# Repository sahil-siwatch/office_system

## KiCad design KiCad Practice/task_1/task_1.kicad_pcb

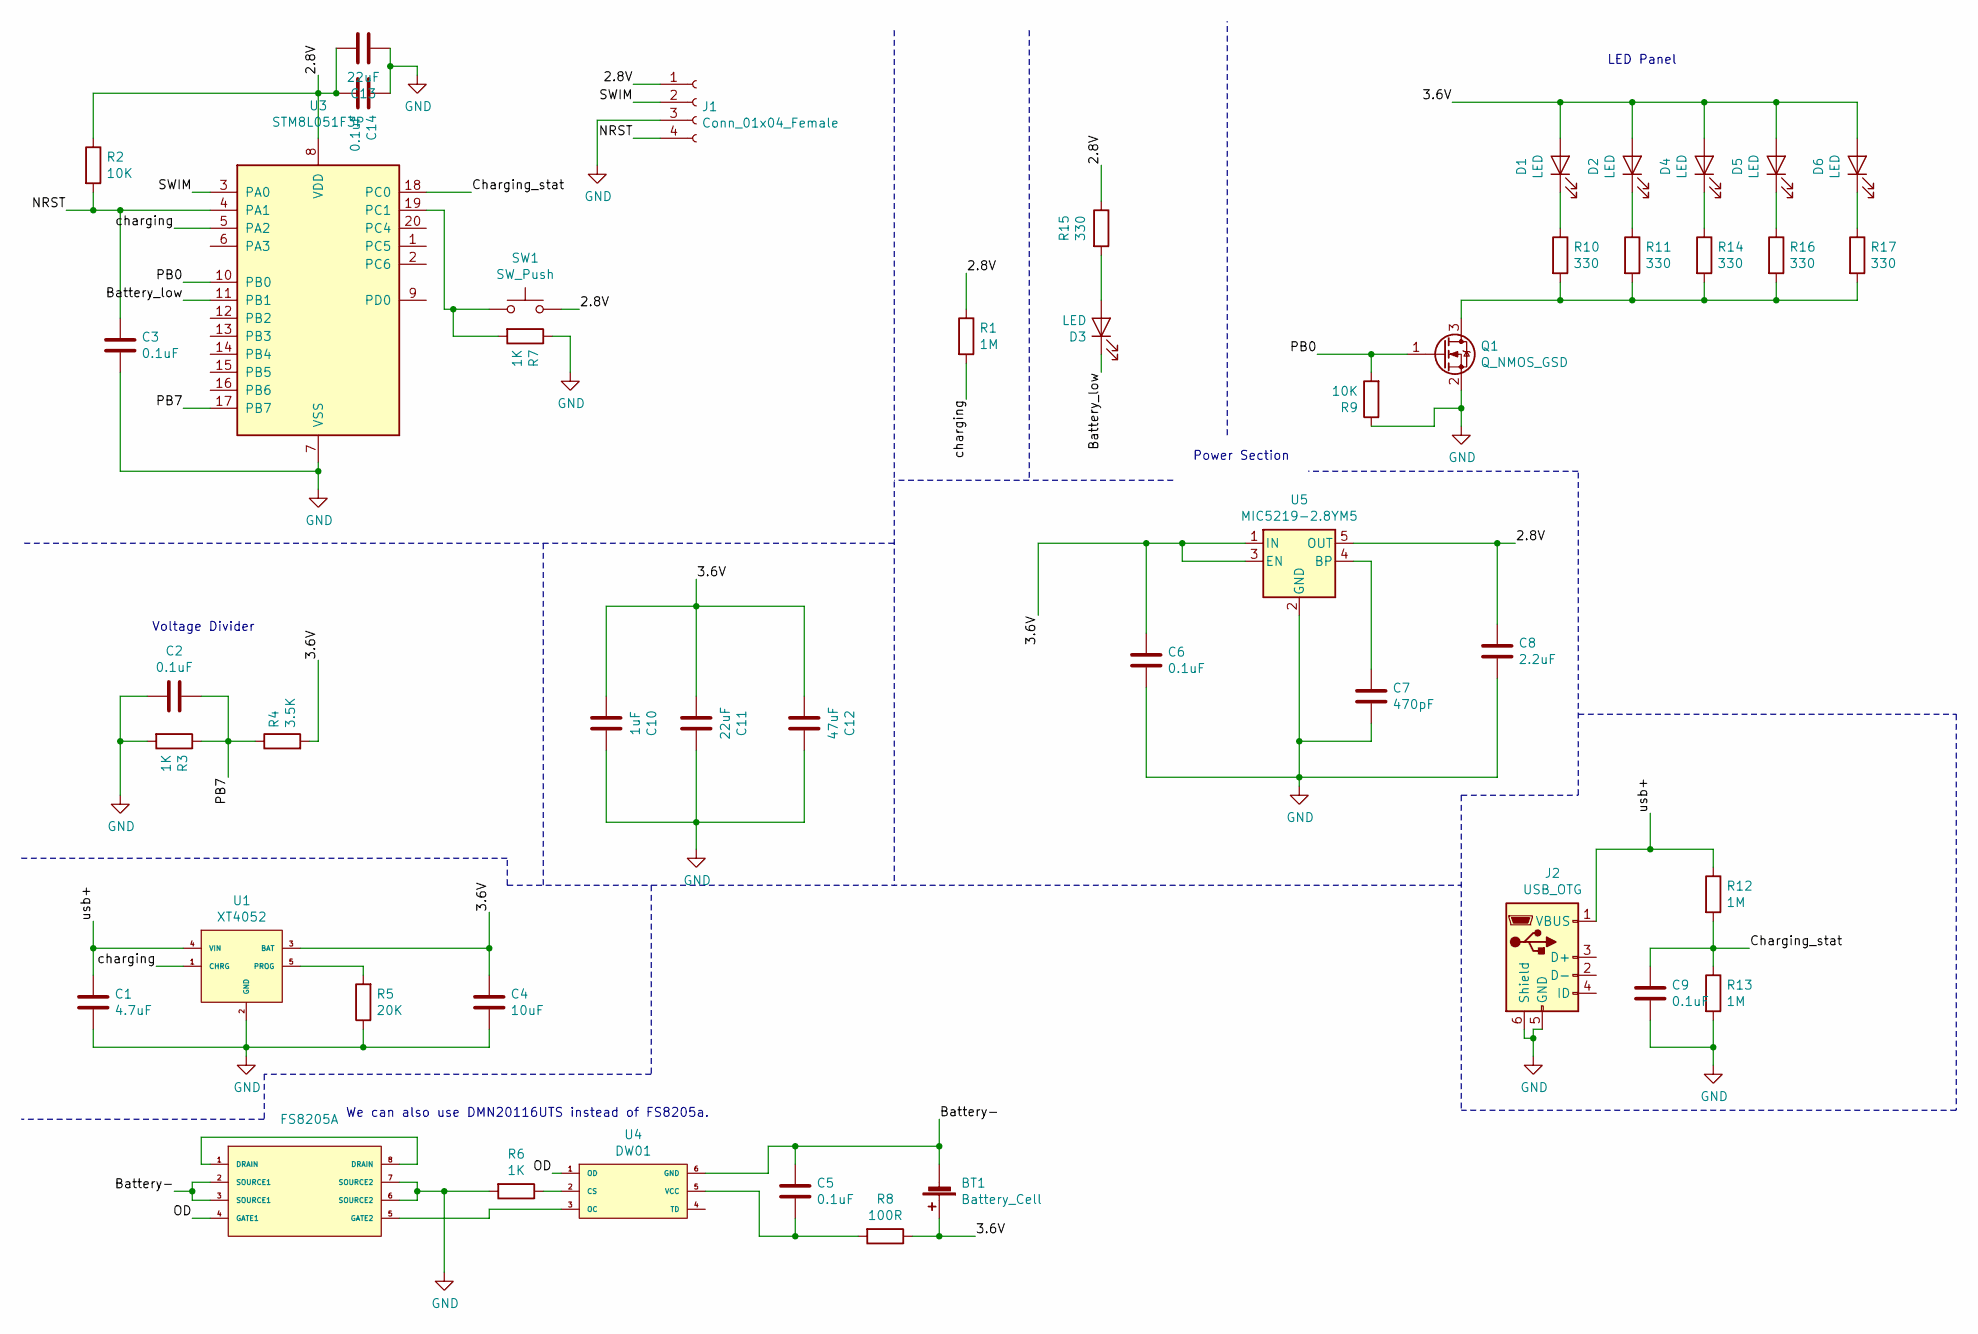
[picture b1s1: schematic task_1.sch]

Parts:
BT1: Battery_Cell; lir2477
C1: 4.7uF; C_0603_1608Metric
C2, C3, C5, C6, C9, C14: 0.1uF; C_0603_1608Metric
C4: 10uF; C_0603_1608Metric
C7: 470pF; C_0603_1608Metric
C8: 2.2uF; C_0603_1608Metric
C10: 1uF; C_0603_1608Metric
C11, C13: 22uF; C_0805_2012Metric
C12: 47uF; C_0805_2012Metric
D1, D2, D3, D4, D5, D6: LED; LED_0805_2012Metric
J1: Conn_01x04_Female; PinHeader_1x04_P2.54mm_Vertical
J2: USB_OTG; USB_Micro-B_Molex-105017-0001
Q1: Q_NMOS_GSD; SOT-23-3
R1, R12, R13: 1M; R_0603_1608Metric
R2, R9: 10K; R_0603_1608Metric
R3, R6, R7: 1K; R_0603_1608Metric
R4: 3.5K; R_0603_1608Metric
R5: 20K; R_0603_1608Metric
R8: 100R; R_0603_1608Metric
R10, R11, R14, R15, R16, R17: 330; R_0603_1608Metric
SW1: SW_Push; SW_PUSH_6mm
U1: XT4052
U2: FS8205A; FS8205a
U3: STM8L051F3P; TSSOP-20_4.4x6.5mm_P0.65mm
U4: DW01
U5: MIC5219-2.8YM5; SOT-23-5

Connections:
/2.8V: C8.1, C13.2, C14.2, J1.1, R1.1, R2.1, R15.1, SW1.2, U3.8 (VDD), U5.5 (OUT)
/3.6V: BT1.1 (+), C4.1, C6.1, C10.1, C11.1, C12.1, D1.2 (A), D2.2 (A), D4.2 (A), D5.2 (A), D6.2 (A), R4.2, R8.1, U1.3 (BAT), U5.1 (IN), U5.3 (EN)
/Battery-: BT1.2 (-), C5.1, U2.2 (SOURCE1), U2.3 (SOURCE1), U4.6 (GND)
/Battery_low: D3.1 (K), U3.11 (PB1)
/Charging_stat: C9.1, R12.2, R13.1, U3.18 (PC0)
/NRST: C3.1, J1.4, R2.2, U3.4 (PA1)
/OD: U2.4 (GATE1), U4.1 (OD)
/PB0: Q1.1 (G), R9.2, U3.10 (PB0)
/PB7: C2.2, R3.1, R4.1, U3.17 (PB7)
/SWIM: J1.2, U3.3 (PA0)
/charging: R1.2, U1.1 (CHRG), U3.5 (PA2)
/usb+: C1.1, J2.1 (VBUS), R12.1, U1.4 (VIN)
GND: C1.2, C2.1, C3.2, C4.2, C6.2, C7.2, C8.2, C9.2, C10.2, C11.2, C12.2, C13.1, C14.1, J1.3, J2.5 (GND), J2.6 (Shield), Q1.2 (S), R3.2, R5.1, R6.2, R7.1, R9.1, R13.2, U1.2 (GND), U2.6 (SOURCE2), U2.7 (SOURCE2), U3.7 (VSS), U5.2 (GND)
unnamed: C5.2, R8.2, U4.5 (VCC)
unnamed: C7.1, U5.4 (BP)
unnamed: D1.1 (K), R10.1
unnamed: D2.1 (K), R11.1
unnamed: D3.2 (A), R15.2
unnamed: D4.1 (K), R14.1
unnamed: D5.1 (K), R16.1
unnamed: D6.1 (K), R17.1
unnamed: Q1.3 (D), R10.2, R11.2, R14.2, R16.2, R17.2
unnamed: R5.2, U1.5 (PROG)
unnamed: R6.1, U4.2 (CS)
unnamed: R7.2, SW1.1, U3.19 (PC1)
unnamed: U2.1 (DRAIN), U2.8 (DRAIN)
unnamed: U2.5 (GATE2), U4.3 (OC)

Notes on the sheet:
Power Section
Voltage Divider
LED Panel
We can also use DMN20116UTS instead of FS8205a.

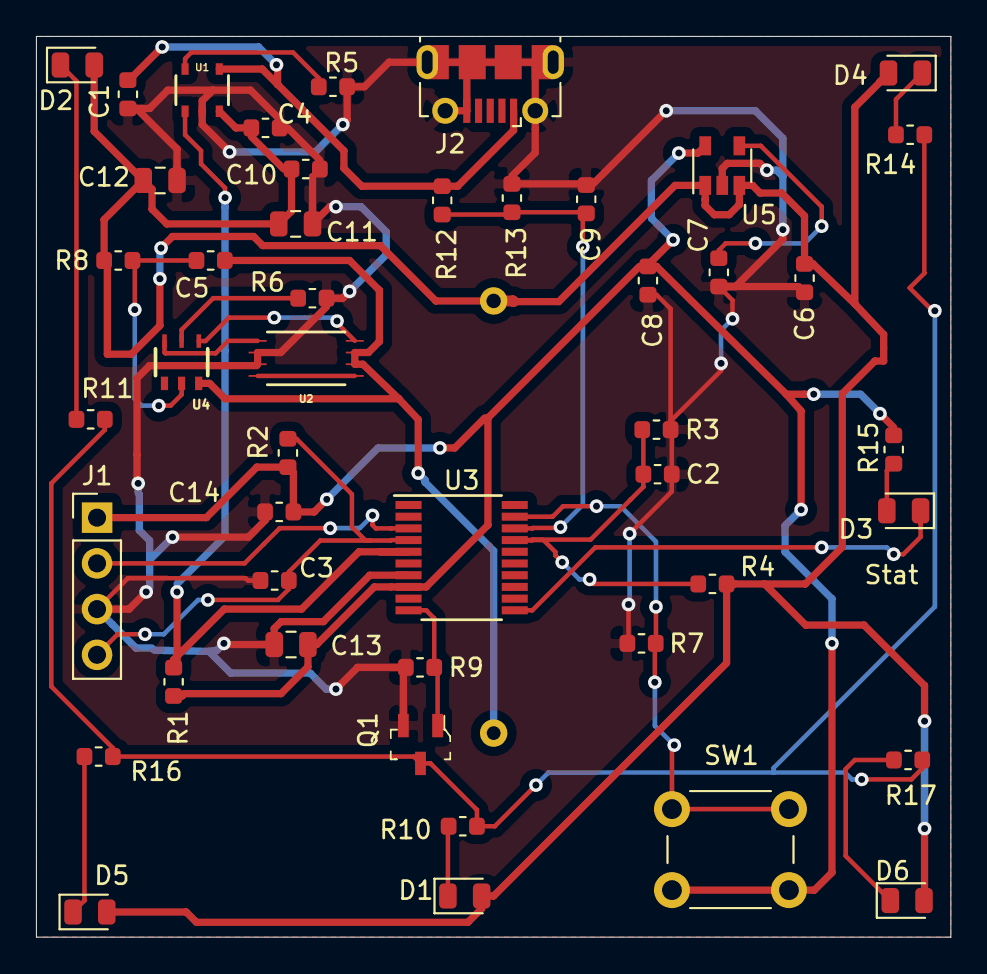
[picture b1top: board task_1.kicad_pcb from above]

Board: 2 copper layers, 50.8 x 50.0 mm, 47 parts (1 on the bottom side), 27 nets.

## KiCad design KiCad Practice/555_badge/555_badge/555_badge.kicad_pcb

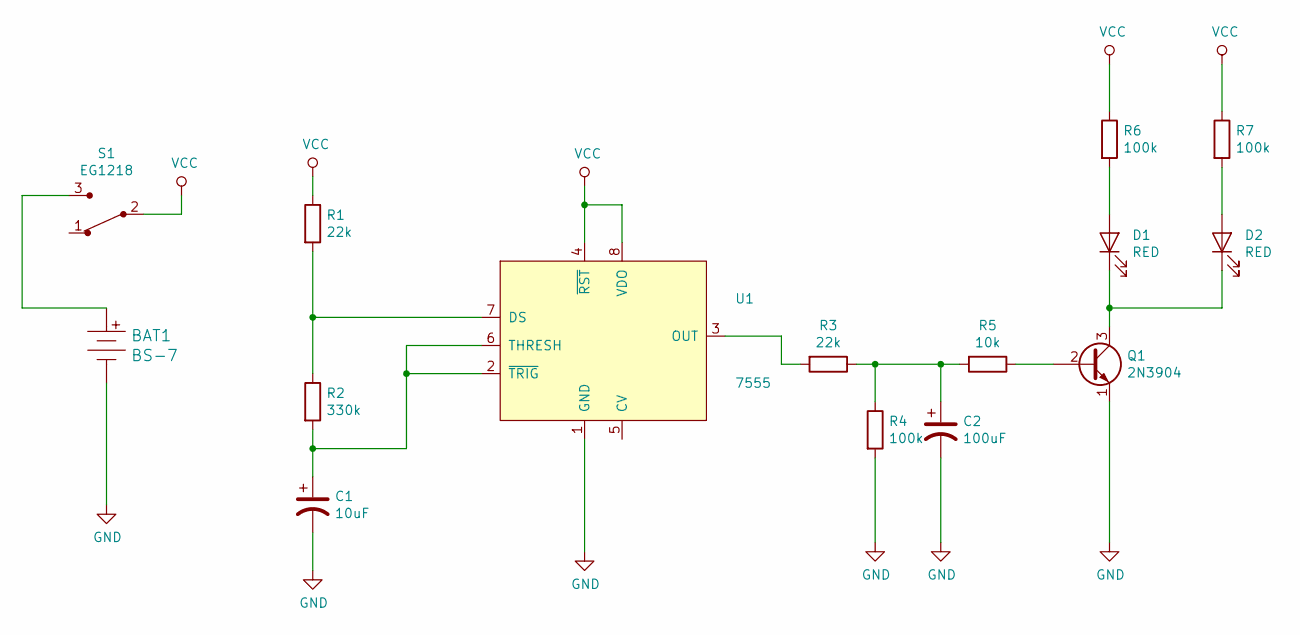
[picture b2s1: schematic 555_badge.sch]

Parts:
BAT1: BS-7; Battery_Holder_Coin_2032_BS-7; MPN BS-7; Digi-Key_PN BS-7-ND
C1: 10uF; CP_Radial_D5.0mm_P2.00mm
C2: 100uF; CP_Radial_D6.3mm_P2.50mm
D1, D2: RED; LED_D3.0mm
Q1: 2N3904; TO-92_Inline
R1, R3: 22k; R_Axial_DIN0207_L6.3mm_D2.5mm_P7.62mm_Horizontal
R2: 330k; R_Axial_DIN0207_L6.3mm_D2.5mm_P7.62mm_Horizontal
R4, R6, R7: 100k; R_Axial_DIN0207_L6.3mm_D2.5mm_P7.62mm_Horizontal
R5: 10k; R_Axial_DIN0207_L6.3mm_D2.5mm_P7.62mm_Horizontal
S1: EG1218; Switch_Slide_11.6x4mm_EG1218; MPN EG1218; Digi-Key_PN EG1903-ND
U1: 7555; ICM7555-PDIP

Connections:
GND: BAT1.Neg, C1.2, C2.2, Q1.1 (E), R4.2, U1.1 (GND)
unnamed: BAT1.Pos, S1.3
unnamed: C1.1, R2.2, U1.2 (~TRIG), U1.6 (THRESH)
unnamed: C2.1, R3.1, R4.1, R5.2
unnamed: D1.1 (K), D2.1 (K), Q1.3 (C)
unnamed: D1.2 (A), R6.2
unnamed: D2.2 (A), R7.2
unnamed: Q1.2 (B), R5.1
unnamed: R1.2, R2.1, U1.7 (DS)
unnamed: R3.2, U1.3 (OUT)
VCC: R1.1, R6.1, R7.1, S1.2, U1.4 (~RST), U1.8 (VDO)

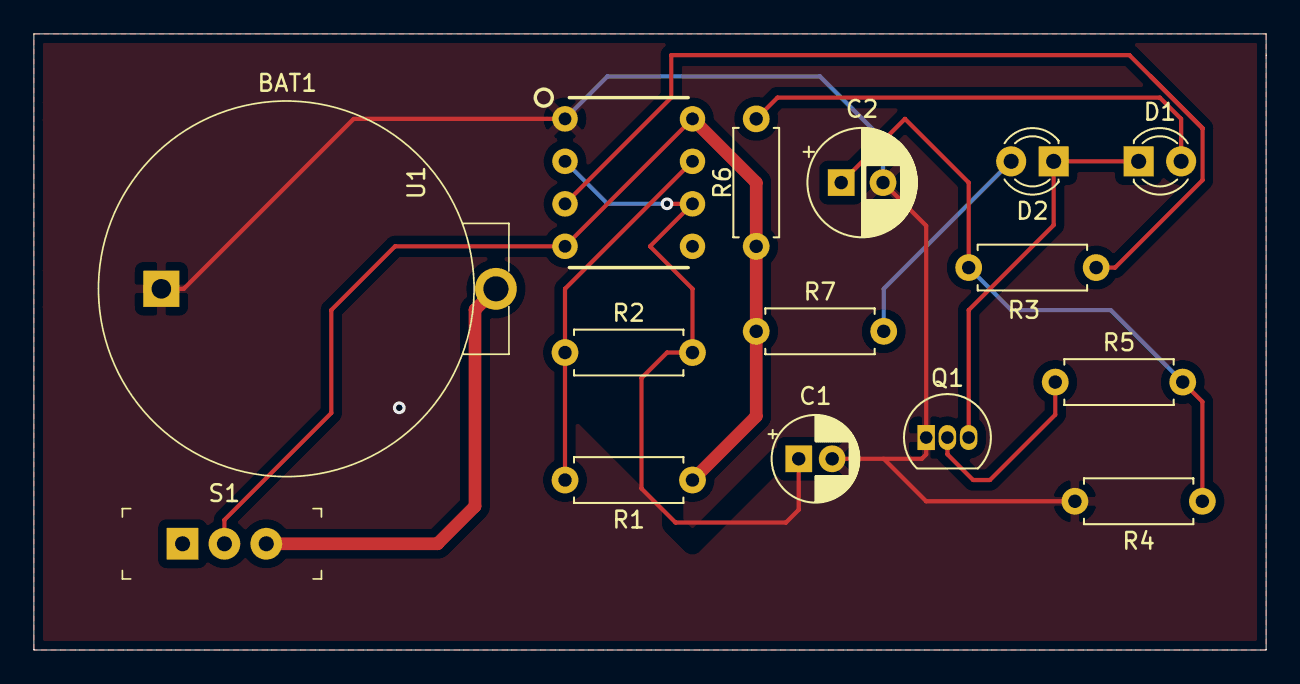
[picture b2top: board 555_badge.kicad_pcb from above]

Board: 2 copper layers, 73.7 x 36.8 mm, 15 parts (0 on the bottom side), 11 nets.

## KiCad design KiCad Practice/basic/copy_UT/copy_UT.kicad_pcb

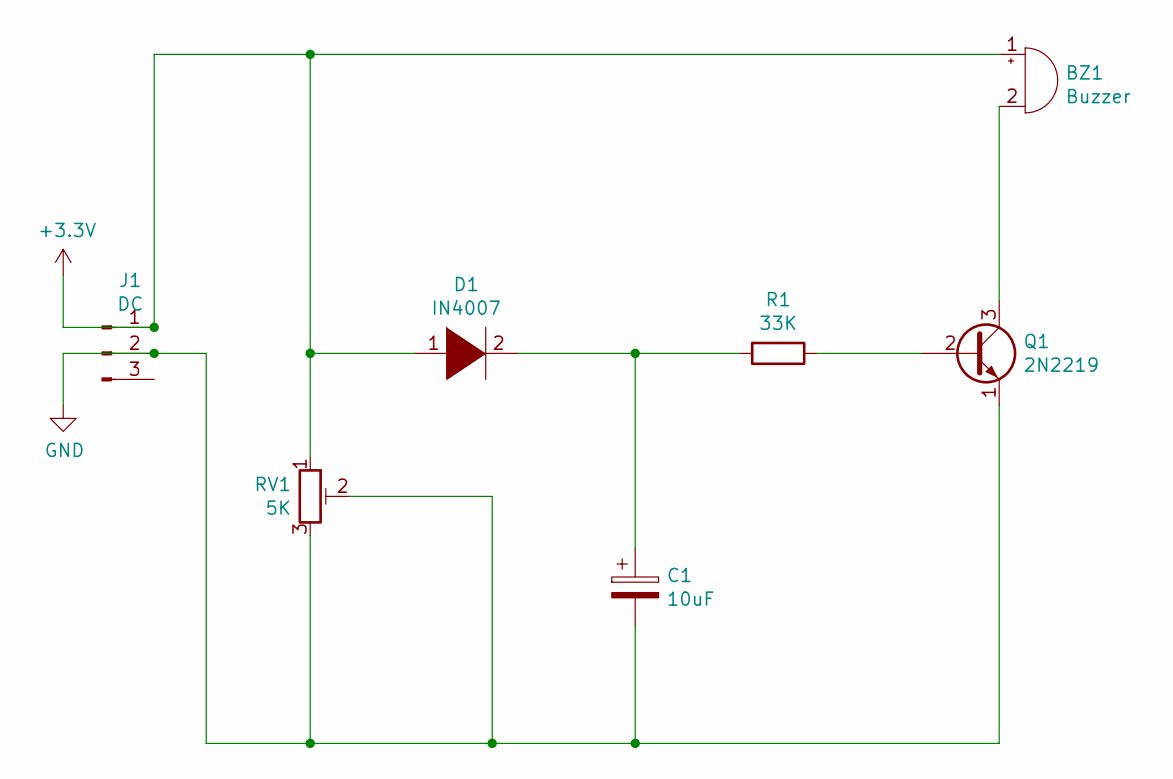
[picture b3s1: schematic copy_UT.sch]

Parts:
BZ1: Buzzer; Buzzer_12x9.5RM7.6
C1: 10uF; CP_Radial_D10.0mm_P3.50mm
D1: IN4007; D_5W_P10.16mm_Horizontal
J1: DC; BarrelJack_Horizontal
Q1: 2N2219; TO-39-3
R1: 33K; R_Axial_DIN0411_L9.9mm_D3.6mm_P12.70mm_Horizontal
RV1: 5K; Potentiometer_ACP_CA6-H2,5_Horizontal

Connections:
+3V3: BZ1.1 (-), D1.1 (K), J1.1, RV1.1
GND: C1.2, J1.2, Q1.1 (E), RV1.2, RV1.3
unnamed: BZ1.2 (+), Q1.3 (C)
unnamed: C1.1, D1.2 (A), R1.2
unnamed: Q1.2 (B), R1.1

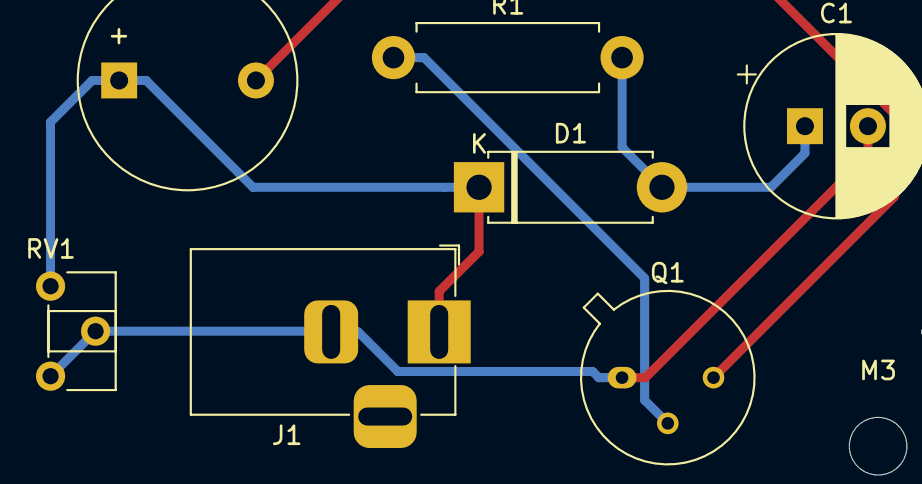
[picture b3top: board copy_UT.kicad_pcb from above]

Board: 2 copper layers, 10 parts (0 on the bottom side), 5 nets.

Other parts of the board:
M1, M2, M3: MountingHole_3.2mm_M3

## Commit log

2020-02-14 folders added
2020-02-14 stm8 datasheet added
2020-02-14 task1_added
2020-02-14 schematic complete
2020-02-15 made schematic
2020-02-16 xt4052_fp made
2020-02-16 finished footprint
2020-02-17 pcb_placement started
2020-02-19 stm8L started
2020-02-20 led_blinked
2020-02-21 switch and interrupts added.
2020-02-23 timer done
2020-02-24 main project started, issues onn
2020-02-25 uart done and adc added
2020-02-26 adc done with stability
2020-02-27 PWM done
2020-02-28 PWM finished and LP started
2020-03-03 source code of project added
2020-03-05 project code added
2020-03-09 new project documentation added
